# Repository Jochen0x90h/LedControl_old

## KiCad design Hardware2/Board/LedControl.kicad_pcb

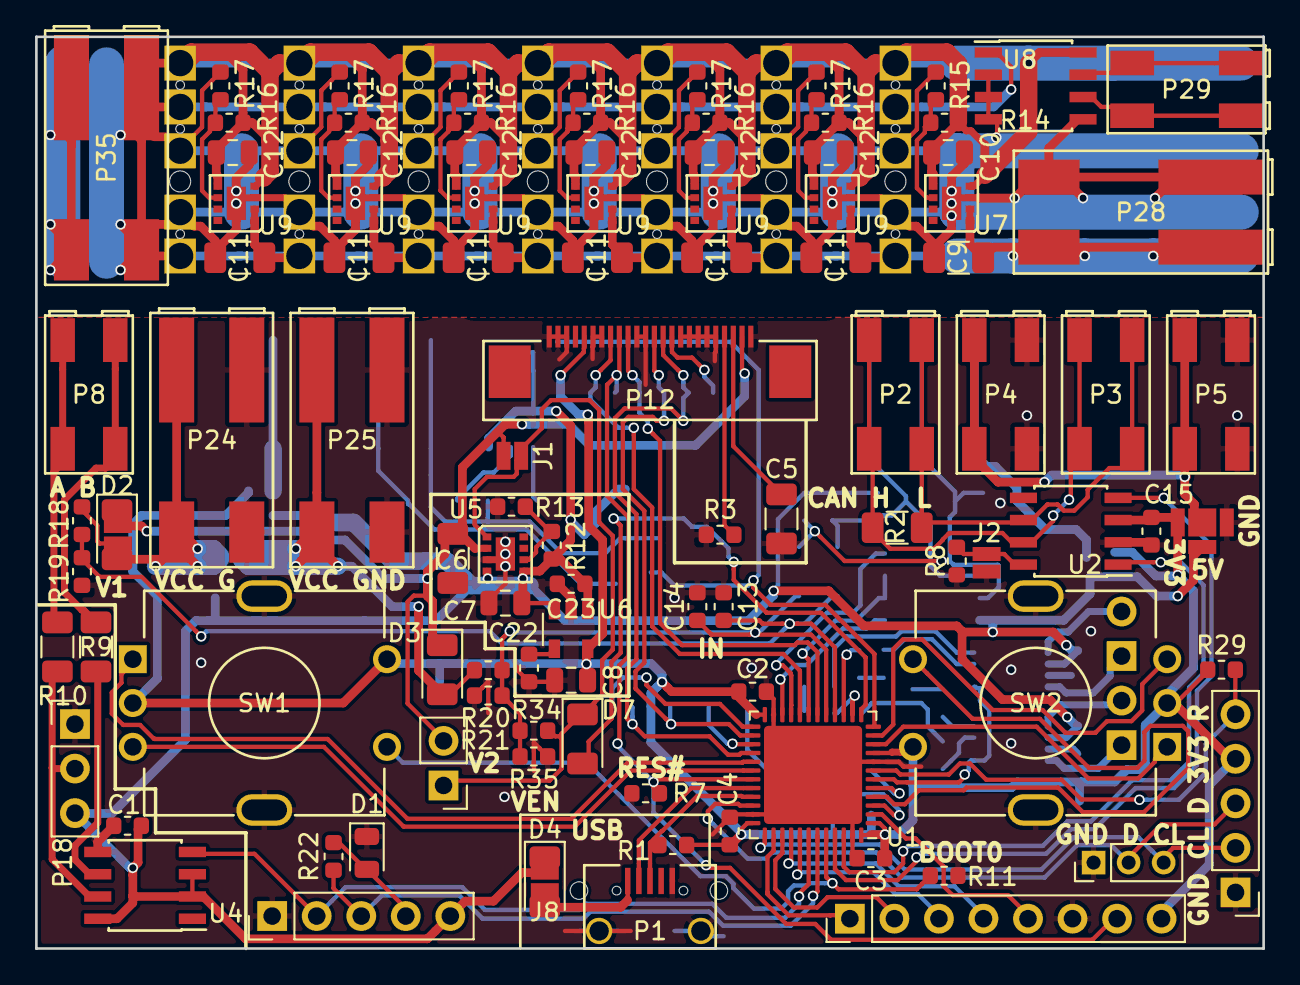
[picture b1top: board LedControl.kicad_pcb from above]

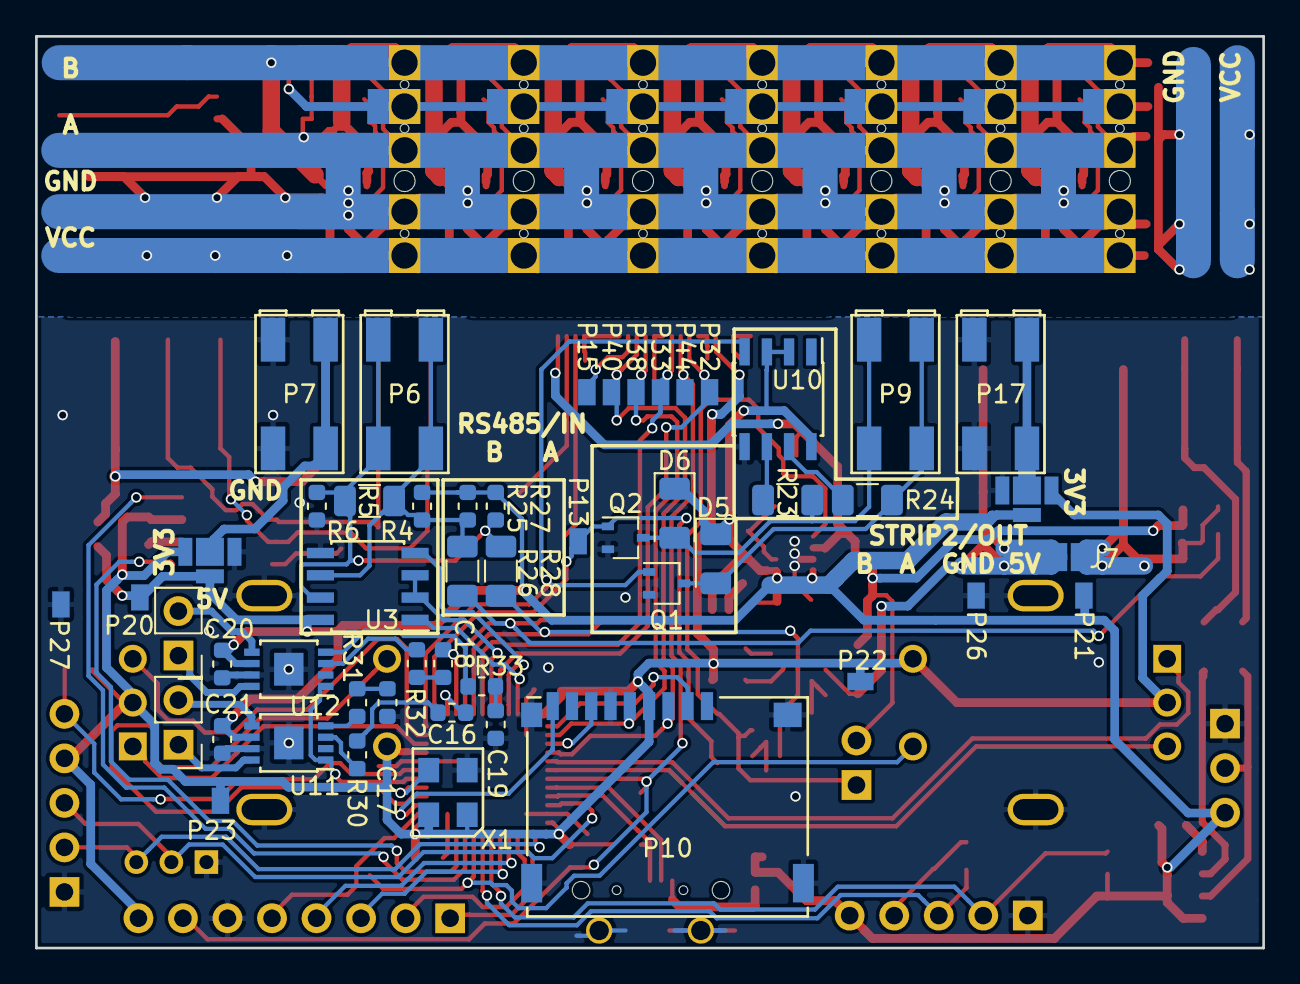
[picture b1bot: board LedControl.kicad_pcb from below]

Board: 2 copper layers, 70.0 x 52.0 mm, 163 parts (51 on the bottom side), 91 nets.

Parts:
C1, C2, C3, C4, C13, C14, C15, C20, C21, C23: 100n; C_0603_1608Metric
C5, C6, C9, C11, C11#2, C11#3, C11#4, C11#5, C11#6: 10u; C_1206_3216Metric
C7, C8, C10, C12, C12#2, C12#3, C12#4, C12#5, C12#6: 22u; C_0805_2012Metric
C16, C17, C18, C19: 100p; C_0603_1608Metric
C22: 10n; C_0603_1608Metric
D1: LED; LED_0805_2012Metric
D2, D3, D4, D5, D6, D7: SD1206S020S1R0; D_1206_3216Metric
DIVIDER1, DIVIDER2, DIVIDER3: Divider_22mm
J1, J2, J6, J7, J8: Jumper
J3, J4, J5: Jumper; Jumper3
P1: Micro_USB
P2, P3, P4, P5, P6, P7, P8, P9, P17, P29: 2059-302; WAGO_2059-302
P10: Micro_SD
P11, P16: Header; PinHeader_1x05_P2.54mm_Vertical
P12: DISPLAY; Connector_Flat_24_Pitch0.50mm
P13, P15, P20, P21, P22, P23, P26, P27, P32, P33, P38, P40, P44: TP; Pad
P14: TMM-103-03-G-S; PinHeader_1x03_P2.00mm_Vertical
P18: CONN_01X03; PinHeader_1x03_P2.54mm_Vertical
P19, P45, P46: Header; PinHeader_1x02_P2.54mm_Vertical
P24, P25, P28, P35: 2060-452; WAGO_2060-452
P30, P31, P31#2, P31#3, P31#4, P31#5, P31#6: LED_Strip
P37: Header; PinHeader_1x08_P2.54mm_Vertical
Q1, Q2: DMG1012UW; SOT-323_SC-70
R1: 1k5; R_0603_1608Metric
R2, R5, R9, R10, R23, R24, R26, R28: 120R; R_1206_3216Metric
R3: 1M2; R_0603_1608Metric
R4, R6, R22: 390R; R_0603_1608Metric
R7, R12, R14, R16, R16#2, R16#3, R16#4, R16#5, R16#6, R18, R20, R34: 52k3; R_0603_1608Metric
R8, R11, R13, R15, R17, R17#2, R17#3, R17#4, R17#5, R17#6, R19, R21, R25, R27, R29, R35: 10k; R_0603_1608Metric
R30, R31, R32, R33: 150k; R_0603_1608Metric
SW1, SW2: PEC12R-4215F-S0024; ALPS_BOURNS_EC12
U1: STM32L433CCUx; QFN-48-1EP_7x7mm_P0.5mm_EP5.6x5.6mm
U2: SN65HVD230; SOIC-8_3.9x4.9mm_P1.27mm
U3, U4, U8, U10: SP485CN; SOIC-8_3.9x4.9mm_P1.27mm
U5, U7, U9, U9#2, U9#3, U9#4, U9#5, U9#6: TPS82130
U6: LP2985IM5-3.3; SOT-23-5
U11, U12: TPA2005; MSOP-8-1EP_3x3mm_P0.65mm_EP1.68x1.88mm
X1: IQXO/7X; Oscillator_5x3.2mm

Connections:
+3V3: C2.1, C3.1, C4.1, C8.1, C15.1, J3.2, J4.2, J5.2, P10.4, P11.4, P12.5, P22.1, P23.1, P37.8, R1.2, R29.2, SW1.2, SW1.4, SW2.2, SW2.4, U1.1, U1.9, U1.24, U1.36, U1.48, U2.3, U6.5, X1.1, X1.4
+5V: C1.1, C7.1, C20.1, C21.1, C23.1, D4.1, D5.1, D6.1, J3.3, J4.3, J5.3, J8.2, P16.5, P18.3, P20.1, P21.1, R4.1, R12.1, R25.1, R27.1, U3.8, U4.2, U4.3, U4.8, U5.4, U5.5, U6.1, U6.3, U10.2, U10.3, U10.8, U11.6, U12.6
+5VD: C10.1, C12.1, C12#2.1, C12#3.1, C12#4.1, C12#5.1, C12#6.1, P30.5, P31.5, P31#2.5, P31#3.5, P31#4.5, P31#5.5, P31#6.5, R14.1, R16.1, R16#2.1, R16#3.1, R16#4.1, R16#5.1, R16#6.1, U7.4, U7.5, U8.8, U9.4, U9.5, U9#2.4, U9#2.5, U9#3.4, U9#3.5, U9#4.4, U9#4.5, U9#5.4, U9#5.5, U9#6.4, U9#6.5
/Power/EN: D7.1, J1.1, P19.1, R34.1, U5.1
AUDIO1: C16.2, U1.14
AUDIO2: C18.2, U1.15
CANH: P2.2, P3.2, R2.1, U2.7
CANL: P2.1, P3.1, R2.2, U2.6
CAN_RX: U1.45, U2.4
CAN_TX: U1.46, U2.1
DISP_D_C#: P12.10, P33.1, U1.18
DISP_NSS: P12.8, P32.1, U1.20
DISP_RFID_RES#: P12.9, P37.7, P44.1, R7.2, U1.31
DISP_SD_MOSI: P10.3, P12.14, P40.1, U1.28
DISP_SD_SCK: P10.5, P12.13, P38.1, U1.26
ENC1_CH1: SW1.1, U1.29
ENC1_CH2: SW1.3, U1.30
ENC1_SW: R11.2, SW1.5, U1.44
ENC2_CH1: SW2.1, U1.10
ENC2_CH2: SW2.3, U1.11
ENC2_SW: SW2.5, U1.4
GND: C1.2, C2.2, C3.2, C4.2, C5.2, C6.2, C7.2, C8.2, C13.2, C14.2, C15.2, C17.2, C19.2, C20.2, C21.2, C22.2, C23.2, D1.1, J2.1, J3.4, J4.4, J5.4, P1.5, P1.6, P4.1, P5.1, P7.2, P10.6, P10.10, P11.1, P12.1, P12.2, P12.3, P12.6, P12.7, P12.11, P12.12, P12.16, P12.17, P12.18, P12.19, P12.20, P12.24, P14.1, P16.1, P17.2, P18.1, P24.1, P25.1, P26.1, P27.1, P37.6, Q1.2, Q2.2, R3.1, R6.2, R7.1, R8.2, R11.1, R13.2, R19.2, R21.2, R35.2, SW1.6, SW2.6, U1.8, U1.23, U1.35, U1.47, U1.49, U2.2, U3.5, U4.5, U5.3, U5.9, U6.2, U10.5, U11.7, U11.9, U12.7, U12.9, X1.2
GNDD: C9.2, C10.2, C11.2, C11#2.2, C11#3.2, C11#4.2, C11#5.2, C11#6.2, C12.2, C12#2.2, C12#3.2, C12#4.2, C12#5.2, C12#6.2, P28.2, P30.2, P30.3, P31.2, P31.3, P31#2.2, P31#2.3, P31#3.2, P31#3.3, P31#4.2, P31#4.3, P31#5.2, P31#5.3, P31#6.2, P31#6.3, P35.1, R15.2, R17.2, R17#2.2, R17#3.2, R17#4.2, R17#5.2, R17#6.2, U7.3, U7.9, U8.2, U8.3, U8.4, U8.5, U9.3, U9.9, U9#2.3, U9#2.9, U9#3.3, U9#3.9, U9#4.3, U9#4.9, U9#5.3, U9#5.9, U9#6.3, U9#6.9
IN1: C13.1, R18.2, R19.1, R26.1, U1.16
IN2: C14.1, R20.2, R21.1, R28.1, R34.2, R35.1, U1.17
LED_TTY_RX: P16.3, R22.1, U1.43
NRST: P11.5, R29.1, U1.7
unnamed: C5.1, P12.22
unnamed: C9.1, C11.1, C11#2.1, C11#3.1, C11#4.1, C11#5.1, C11#6.1, P28.1, P30.1, P31.1, P31#2.1, P31#3.1, P31#4.1, P31#5.1, P31#6.1, P35.2, U7.1, U7.2, U9.1, U9.2, U9#2.1, U9#2.2, U9#3.1, U9#3.2, U9#4.1, U9#4.2, U9#5.1, U9#5.2, U9#6.1, U9#6.2
unnamed: C16.1, R30.2
unnamed: C17.1, R31.2
unnamed: C18.1, R32.2
unnamed: C19.1, R33.2
unnamed: C22.1, U6.4
unnamed: D1.2, P16.4, R22.2
unnamed: D2.2, J6.1, J7.2, P24.2, R18.1
unnamed: D3.2, J7.1, P25.2, R20.1
unnamed: D4.2, J8.1, P1.1
unnamed: J2.2, R8.1, U2.8
unnamed: J3.1, P4.2, P5.2
unnamed: J4.1, P7.1
unnamed: J5.1, P17.1
unnamed: P12.15, P15.1
unnamed: P12.21, R3.2
unnamed: P18.2, R10.1, U4.7
unnamed: P29.1, U8.6
unnamed: P29.2, U8.7
unnamed: P30.4, P31.4, P31#2.4, P31#3.4, P31#4.4, P31#5.4, P31#6.4, U8.1
unnamed: P45.1, U11.8
unnamed: P45.2, U11.5
unnamed: P46.1, U12.8
unnamed: P46.2, U12.5
unnamed: R9.1, U4.6
unnamed: R12.2, R13.1, U5.6
unnamed: R14.2, R15.1, U7.6
unnamed: R16.2, R16#2.2, R16#3.2, R16#4.2, R16#5.2, R16#6.2, R17.1, R17#2.1, R17#3.1, R17#4.1, R17#5.1, R17#6.1, U9.6, U9#2.6, U9#3.6, U9#4.6, U9#5.6, U9#6.6
unnamed: R23.1, U10.6
unnamed: R24.1, U10.7
unnamed: R30.1, U11.3
unnamed: R31.1, U11.4
unnamed: R32.1, U12.3
unnamed: R33.1, U12.4
unnamed: U1.5, X1.3
unnamed: U9.7, U9#2.7, U9#3.7, U9#4.7, U9#5.7, U9#6.7
unnamed: U9.8, U9#2.8, U9#3.8, U9#4.8, U9#5.8, U9#6.8
OUT2: D7.2, P13.1, Q2.1, U1.13
RFID_IRQ: P37.5, U1.2
RFID_MISO: P37.4, U1.40
RFID_MOSI: P37.3, U1.41
RFID_NSS: P37.1, U1.38
RFID_SCK: P37.2, U1.39
RS485A: P6.1, R4.2, R5.1, R25.2, R26.2, U3.6
RS485B: P6.2, R5.2, R6.1, R27.2, R28.2, U3.7
RS485_DE: U1.19, U3.2, U3.3
RS485_RX: U1.22, U3.1
RS485_TX: U1.21, U3.4
SD_DET: P10.9, U1.3
SD_MISO: P10.7, U1.27
SD_NSS: P10.2, U1.25
SHUTDOWN: U1.6, U11.1, U12.1
STRIP1_A: P8.2, R10.2
STRIP1_B: P8.1, R9.2
STRIP1_TTY_TX: P16.2, U1.42, U4.4
STRIP2_A: D5.2, P9.1, Q1.3, R24.2
STRIP2_B: D6.2, P9.2, Q2.3, R23.2
STRIP2_TX_OUT1: Q1.1, U1.12, U10.4
SWCLK: P11.2, P14.3, U1.37
SWDIO: P11.3, P14.2, U1.34
USB_DM: P1.2, U1.32
USB_DP: P1.3, R1.1, U1.33
VCC: C6.1, D2.1, D3.1, J1.2, J6.2, P12.23, P19.2, U5.2

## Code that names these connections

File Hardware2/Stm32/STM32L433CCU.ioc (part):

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Mcu.Name=STM32L433C(B-C)Ux
Mcu.Package=UFQFPN48
Mcu.UserName=STM32L433CCUx
PA0.GPIOParameters=GPIO_Label
PA0.GPIO_Label=ENC2_TIM2_CH1
PA0.Signal=S_TIM2_CH1
PA1.GPIOParameters=GPIO_Label
PA1.GPIO_Label=ENC2_TIM2_CH2
PA1.Signal=S_TIM2_CH2
PA10.GPIOParameters=GPIO_Label
PA10.GPIO_Label=DISP_D/C\#
PA10.Signal=GPIO_Output
PA11.Mode=Device
PA11.Signal=USB_DM
PA12.Mode=Device
PA12.Signal=USB_DP
PA15\ (JTDI).GPIOParameters=GPIO_Label
PA15\ (JTDI).GPIO_Label=SD_SPI1_NSS
PA15\ (JTDI).Mode=NSS_Signal_Hard_Output
PA15\ (JTDI).Signal=SPI1_NSS
PA2.GPIOParameters=GPIO_Label
PA2.GPIO_Label=STRIP2_USART2_TX
PA2.Mode=Asynchronous
PA2.Signal=USART2_TX
PA3.GPIOParameters=GPIO_Label
PA3.GPIO_Label=STRIP2_USART2_RX
PA3.Mode=Asynchronous
PA3.Signal=USART2_RX
PA5.GPIOParameters=GPIO_Label
PA5.GPIO_Label=SD_SPI1_SCK
PA5.Mode=Full_Duplex_Master
PA5.Signal=SPI1_SCK
PA6.GPIOParameters=GPIO_Label
PA6.GPIO_Label=SD_SPI1_MISO
PA6.Mode=Full_Duplex_Master
PA6.Signal=SPI1_MISO
PA7.GPIOParameters=GPIO_Label
PA7.GPIO_Label=U1_ADC1_IN12
PA7.Signal=ADCx_IN12
PA8.GPIOParameters=GPIO_Label
PA8.GPIO_Label=ENC1_TIM1_CH1
PA8.Signal=S_TIM1_CH1
PA9.GPIOParameters=GPIO_Label
PA9.GPIO_Label=ENC1_TIM1_CH2
PA9.Signal=S_TIM1_CH2
PB0.GPIOParameters=GPIO_Label
PB0.GPIO_Label=U2_ADC1_IN15
PB0.Signal=ADCx_IN15
PB1.GPIOParameters=GPIO_Label
PB1.GPIO_Label=RS485_USART3_DE
PB1.Mode=Hardware Flow Control (RS485)
PB1.Signal=USART3_DE
PB10.GPIOParameters=GPIO_Label
PB10.GPIO_Label=RS485_USART3_TX
PB10.Mode=Asynchronous
PB10.Signal=USART3_TX
PB11.GPIOParameters=GPIO_Label
PB11.GPIO_Label=RS485_USART3_RX
PB11.Mode=Asynchronous
PB11.Signal=USART3_RX
PB12.GPIOParameters=GPIO_Label
PB12.GPIO_Label=DISP_SPI2_NSS
PB12.Mode=NSS_Signal_Hard_Output
PB12.Signal=SPI2_NSS
PB13.GPIOParameters=GPIO_Label
PB13.GPIO_Label=DISP_SPI2_SCK
PB13.Mode=TX_Only_Simplex_Unidirect_Master
PB13.Signal=SPI2_SCK
PB14.GPIOParameters=GPIO_Label
PB14.GPIO_Label=SD_Cd
PB14.Signal=GPIO_Input
PB15.GPIOParameters=GPIO_Label
PB15.GPIO_Label=DISP_SPI2_MOSI
PB15.Mode=TX_Only_Simplex_Unidirect_Master
PB15.Signal=SPI2_MOSI
PB2.GPIOParameters=GPIO_Label
PB2.GPIO_Label=DISP_RES\#
PB2.Signal=GPIO_Output
PB5.GPIOParameters=GPIO_Label
PB5.GPIO_Label=SD_SPI1_MOSI
PB5.Mode=Full_Duplex_Master
PB5.Signal=SPI1_MOSI
PB6.GPIOParameters=GPIO_Label
PB6.GPIO_Label=STRIP1_USART1_TX
PB6.Mode=Asynchronous
PB6.Signal=USART1_TX
PB7.GPIOParameters=GPIO_Label
PB7.GPIO_Label=USART1_RX
PB7.Mode=Asynchronous
PB7.Signal=USART1_RX
PB9.GPIOParameters=GPIO_Label
PB9.GPIO_Label=DEBUG_LED
PB9.Signal=GPIO_Output
PC13.GPIOParameters=PinState,GPIO_Label
PC13.GPIO_Label=STRIP2_DE
PC13.PinState=GPIO_PIN_SET
PC13.Signal=GPIO_Output
PC14-OSC32_IN\ (PC14).GPIOParameters=GPIO_Label
PC14-OSC32_IN\ (PC14).GPIO_Label=ENC1_SW
PC14-OSC32_IN\ (PC14).Signal=GPIO_Input
PC15-OSC32_OUT\ (PC15).GPIOParameters=GPIO_Label
PC15-OSC32_OUT\ (PC15).GPIO_Label=ENC2_SW
PC15-OSC32_OUT\ (PC15).Signal=GPIO_Input
RCC.HSE_VALUE=8000000
RCC.SYSCLKFreq_VALUE=32000000
RCC.SYSCLKSource=RCC_SYSCLKSOURCE_PLLCLK

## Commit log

2017-03-20 adds casing
2017-03-26 finalizes poti holders in wheels and cover
2017-10-03 add board using KiCad
2018-02-09 Finished schematic
2018-04-01 Finished routing main board
2018-04-20 routing nearly finished
2018-05-11 add Emulator and Effects
2018-05-20 Generator generates palettes from files
2018-05-27 Add plasma effect
2018-05-28 Linux compatibility
2018-06-04 add winter, spring and summer effects
2018-06-30 Finish seasons effects
2018-07-17 convert effects to C, add software for ATmega328 (not tested yet)
2018-08-05 Now works on ATmega328
2018-09-01 add schematic of old ATmega based board
2018-12-23 Start software for stm32 based hardware2
2019-02-08 continuing software for stm32
2019-02-20 Update to KiCad 5.0.1, add debug connector
2019-02-27 Board is ready for production, needs last review
2019-03-11 LED strip power supply below strip
2019-05-03 Add CAN bus
2019-05-11 USB and SD card at center
2019-06-07 add rfid and speaker
